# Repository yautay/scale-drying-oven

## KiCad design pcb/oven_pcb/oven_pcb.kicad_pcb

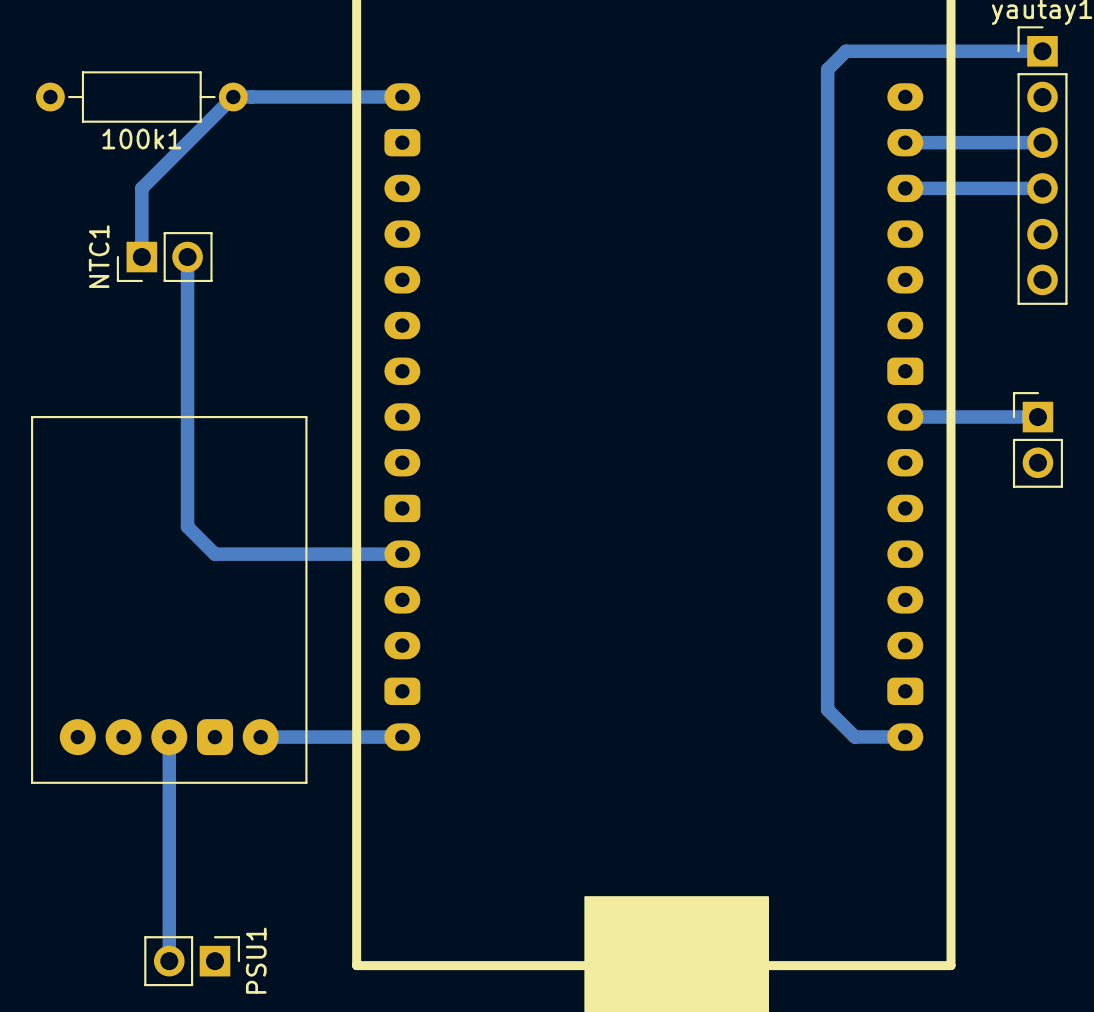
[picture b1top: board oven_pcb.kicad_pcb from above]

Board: 2 copper layers, 7 parts (0 on the bottom side), 9 nets.

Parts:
100k1: R; R_Axial_DIN0207_L6.3mm_D2.5mm_P10.16mm_Horizontal
NTC1: Conn_01x02_Male; PinHeader_1x02_P2.54mm_Vertical
PSU1: Conn_01x02_Male; PinHeader_1x02_P2.54mm_Vertical
U1: D24V10F5; yautay-5V-stepdown
U2: NodeMCU_3.0_(ESP-12E); nodeMCUv3
U3: SSR; PinHeader_1x02_P2.54mm_Vertical
yautay1: BME2803V; PinHeader_1x06_P2.54mm_Vertical

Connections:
+24V: PSU1.2, U1.3
GND: 100k1.2, PSU1.1, U1.4, U2.10, U2.14, U2.17, U2.24, U3.2, yautay1.2
unnamed: 100k1.1, NTC1.1, U2.1
unnamed: NTC1.2, U2.11
unnamed: U1.5, U2.15
unnamed: U2.16, yautay1.1
unnamed: U2.23, U3.1
unnamed: U2.28, yautay1.4
unnamed: U2.29, yautay1.3

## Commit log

2021-10-23 init
2021-10-24 XT60 bracket files
2021-10-24 temp set
2021-10-24 power_state wip
2021-10-24 power_set done
2021-10-24 power_management done
2021-10-24 testready
2021-10-24 heating loop fix
2021-10-27 wifimanager implementation
2021-10-27 wifi manager
2021-10-28 stl legs
2021-10-30 debug
2021-10-31 pcb_v2
2021-11-01 pcb v3
2021-11-06 premiere
2021-11-06 chamber
2021-11-09 wip web_sockets
